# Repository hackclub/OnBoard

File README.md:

# **<h2>Onboard has ended now :/ <br> But much more to come! Stay tuned :). [Sign up here.](https://forms.hackclub.com/t/xtYYcGvNTCus)<h2>**

# OnBoard - Get a $100 grant and make a PCB!

> "I’m so glad that young people can create things like PC boards online. May your creativity have no limits!”
>
> _– [Steve Wozniak](https://en.wikipedia.org/wiki/Steve_Wozniak), Apple co-founder endorsing Hack Club OnBoard_

It's easier than ever for high school students to get involved with programming; all you need is a computing device and internet access. Yet, *it's not the same for hardware*. While PCB fabs have greatly increased the accessibility for professionally done boards, there is still no clear way for high school students to jump in. This is where OnBoard comes in.

---

Every student will receive up to $100 to cover PCB manufacturing costs, and join a community of peers– some more beginner and some more experienced.

## Requirements

Every design/submission needs to meet the following constraints to be approved:

- Unique and open-source design
- Must be orderable on JLCPCB or other [approved vendor](https://github.com/hackclub/OnBoard/blob/main/docs/VENDORS.md)
- Must be in high school or younger[^1][^2][^3] and show proof of school enrollment to submit

[^1]: Home school still counts!
[^2]: If you left high school early you can also submit.
[^3]: If you need help with ideas for proof of age, ask in our Slack and we'll help you out! [here](https://hackclub.com/slack/?event=onboard)

## Getting Started

> You can also go through a video with instructions on how to submit your grant!
>
> 

### Star the repo (Optional)

To follow the repo for updates and show you're participating, click the "star" button on the [`onboard`](https://github.com/hackclub/OnBoard/) repo.

### 1. Join `#electronics` on Slack!

Our [`#electronics`](https://hackclub.slack.com/archives/C0587U78RK4) channel[^4] is where the party is getting started! If you haven't already joined, make sure to add yourself to the channel. And for those who are new to the Hack Club slack, sign up to our community of 13k+ makers through [here](https://hackclub.com/slack/?event=onboard) (don't worry, there isn't an application).

[^4]: This link only works after you've joined the slack. Make sure to get an invite [here](https://hackclub.com/slack/?event=onboard) first.

Perhaps ping a little hello to `@Kevin Yang`?

### 2. Design a Board!

It's design time! If you've done this before, you can skip ahead to step 3. Most people reading this will be new to PCB design, so we've made a simple tutorial on making an example board.

Check out our [PCB tutorials](https://jams.hackclub.com/tag/pcb), where you'll make a design from scratch in a free online editor. This is jumping in the deep end- it won't explain everything, but it will give you a taste of what's possible. By the end you probably won't understand _what_ you did or _why_ you did it, but you will have a working design for a board and you'll know how to **tweak** and **edit** the design to make it your own.

_If you get stuck on these tutorials, or want more example projects to learn from, post in the Slack channel to hear from others going on their journeys._

### 3. Upload to a Vendor and Take a Screenshot

Upload your Gerber files to [JLCPCB.com](https://jlcpcb.com/) and add them to your cart. JLCPCB is the default PCB manufacturer, but you can shop around [^5] if there's a specific one you want to use [^6]. Ensure you complete the checkout process by entering your address and selecting a shipping method. Once completed, take a screenshot with all the final costs and shipping!
> If you're curious what all the settings are about or how to order for assembly, check out our [`ordering_from_JLCPCB.md`](./docs/ordering_from_JLCPCB.md) doc!
> To avoid excess shipping fees or customs, check out [`the Shipping Tips`](./community/shipping.md) doc!

It should look like this:

**Note:** Your screenshot is **VITAL** since your project cannot be approved without it. You'll include the screenshot in your PR later.

[^5]: Don't know which ones you can use? Check out [`VENDORS.md`](./docs/VENDORS.md) for more info!
[^6]: If outside the US you may be charged customs which aren't covered by the grant! Check beforehand.

### 4. Fork!

Fork the [`onboard`](https://github.com/hackclub/OnBoard/) repo! This is the where you'll add your project files and eventually PR from!

### 5. Add Your Design to Your Project Repo

From your fork of `OnBoard`, create a folder with your project name under `OnBoard/projects`. To do this, go to the projects folder and click `Create new file`.

Then in the box labeled `name your file...`, type in `PROJECT_NAME/README.md`. This creates a README file under a folder called named after your project.

After this, copy and paste the contents of [`TEMPLATE.md`](./projects/!Template/TEMPLATE.md?plain=1) into the text editor and fill it out!

Once your done, press the big green `Commit changes` button to save!

With your README filled out, head over to add files to begin uploading your Gerber, design files, and screen shot of vendor approval.

In all, you should have the following files under your project folder:
- [ ] `README.md`: A filled out [`TEMPLATE.md`](./projects/!Template/TEMPLATE.md?plain=1), renamed to `README.md`
- [ ] `cart.png`: A [screenshot](./docs/images/ordering/cart.png) of your order details
- [ ] `gerber.zip`: This should be the file that you send off to the vendor.
- [ ] `schematic.pdf`: Export the schematic from your EDA program as a PDF.
    - Go to "File > Export > PDF" **in EasyEDA's Schematic tab** for this.
- [ ] `src/`: Make a folder called `src` and Whatever format your designer outputs should be included.
    - For **EasyEDA STD**, you need to File > Export > EasyEDA two JSON files - one from the schematic tab and one from the PCB tab.
      - *Optionally*, for EasyEDA STD, export a 3D Model as `.obj` as save it to the `/src` folder 

    - For **KiCad**, read the [Submitting for KiCad](docs/kicad-submission.md), add the `.kicad_pcb`, `.kicad_sch` and `.kicad_pro` files to your `/src` folder.
      - What is **KiCad**? See [KiCad for Beginners](docs/KiCad_Beginner_Guide.md) for a mini tutorial on how to use.
    - Or `design.json`, `design.sch`, `design.brd`, etc for other PCB Editors.

Ensure your file names are exactly the same as above.

Your PR should have a structure like this:

| EasyEDA STD | KiCad |
| ----------- | ----------- |
 | 
----

If you have all the above, you're done with this step!

### 6. Create a PR!

Once you've uploaded your files, you can merge them to the main repo through a pull request! Under the contribute tab of your forked repo, click the big green `Open pull request`.

That will bring you to the main repo, where you'll initiate a pull request. Follow the checklist, we'll then review your PR and you'll be off to the races!

### 7. Get approval and order your board!

Once you submit your PR, it needs two approvals:
- One verifying your high school enrollment documents, from HCB.
- Another one from the engineering team, checking that your design follows the grant requirements.

These reviews typically take 24-48 business hours, and if everything is correct, we'll merge your pull request!

After your pull request gets merged, it can take up to 24 business hours for you to receive an email from HCB with a virtual credit card. Make sure to check your spam folder. Then, you can order your board!

### 8. Ship it!

Post photos of your board in [`#electronics`](https://hackclub.slack.com/archives/C056AMWSFKJ)! We can't wait to see what you make!

## Example Projects

- [PCB Business Card with NFC, "Hackercard"](https://jams.hackclub.com/jam/hacker-card)
- [Build a USB Hub](https://jams.hackclub.com/batch/usb-hub)
- [Make a Digital Level](https://jams.hackclub.com/batch/sparkletilt-pcb)

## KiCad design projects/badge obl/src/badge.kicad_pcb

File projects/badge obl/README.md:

---
name: "Souptik Samanta"
slack_handle: "@Souptik Samanta"
github_handle: "@Souptik-Samanta"
tutorial: # Link to the tutorial if you used one
wokwi: # Link to the Wokwi project if you're submitting for Hacky Holidays
---

# YOUR PROJECT NAME

PCB ADGE

17

hard af took so many revs to finish

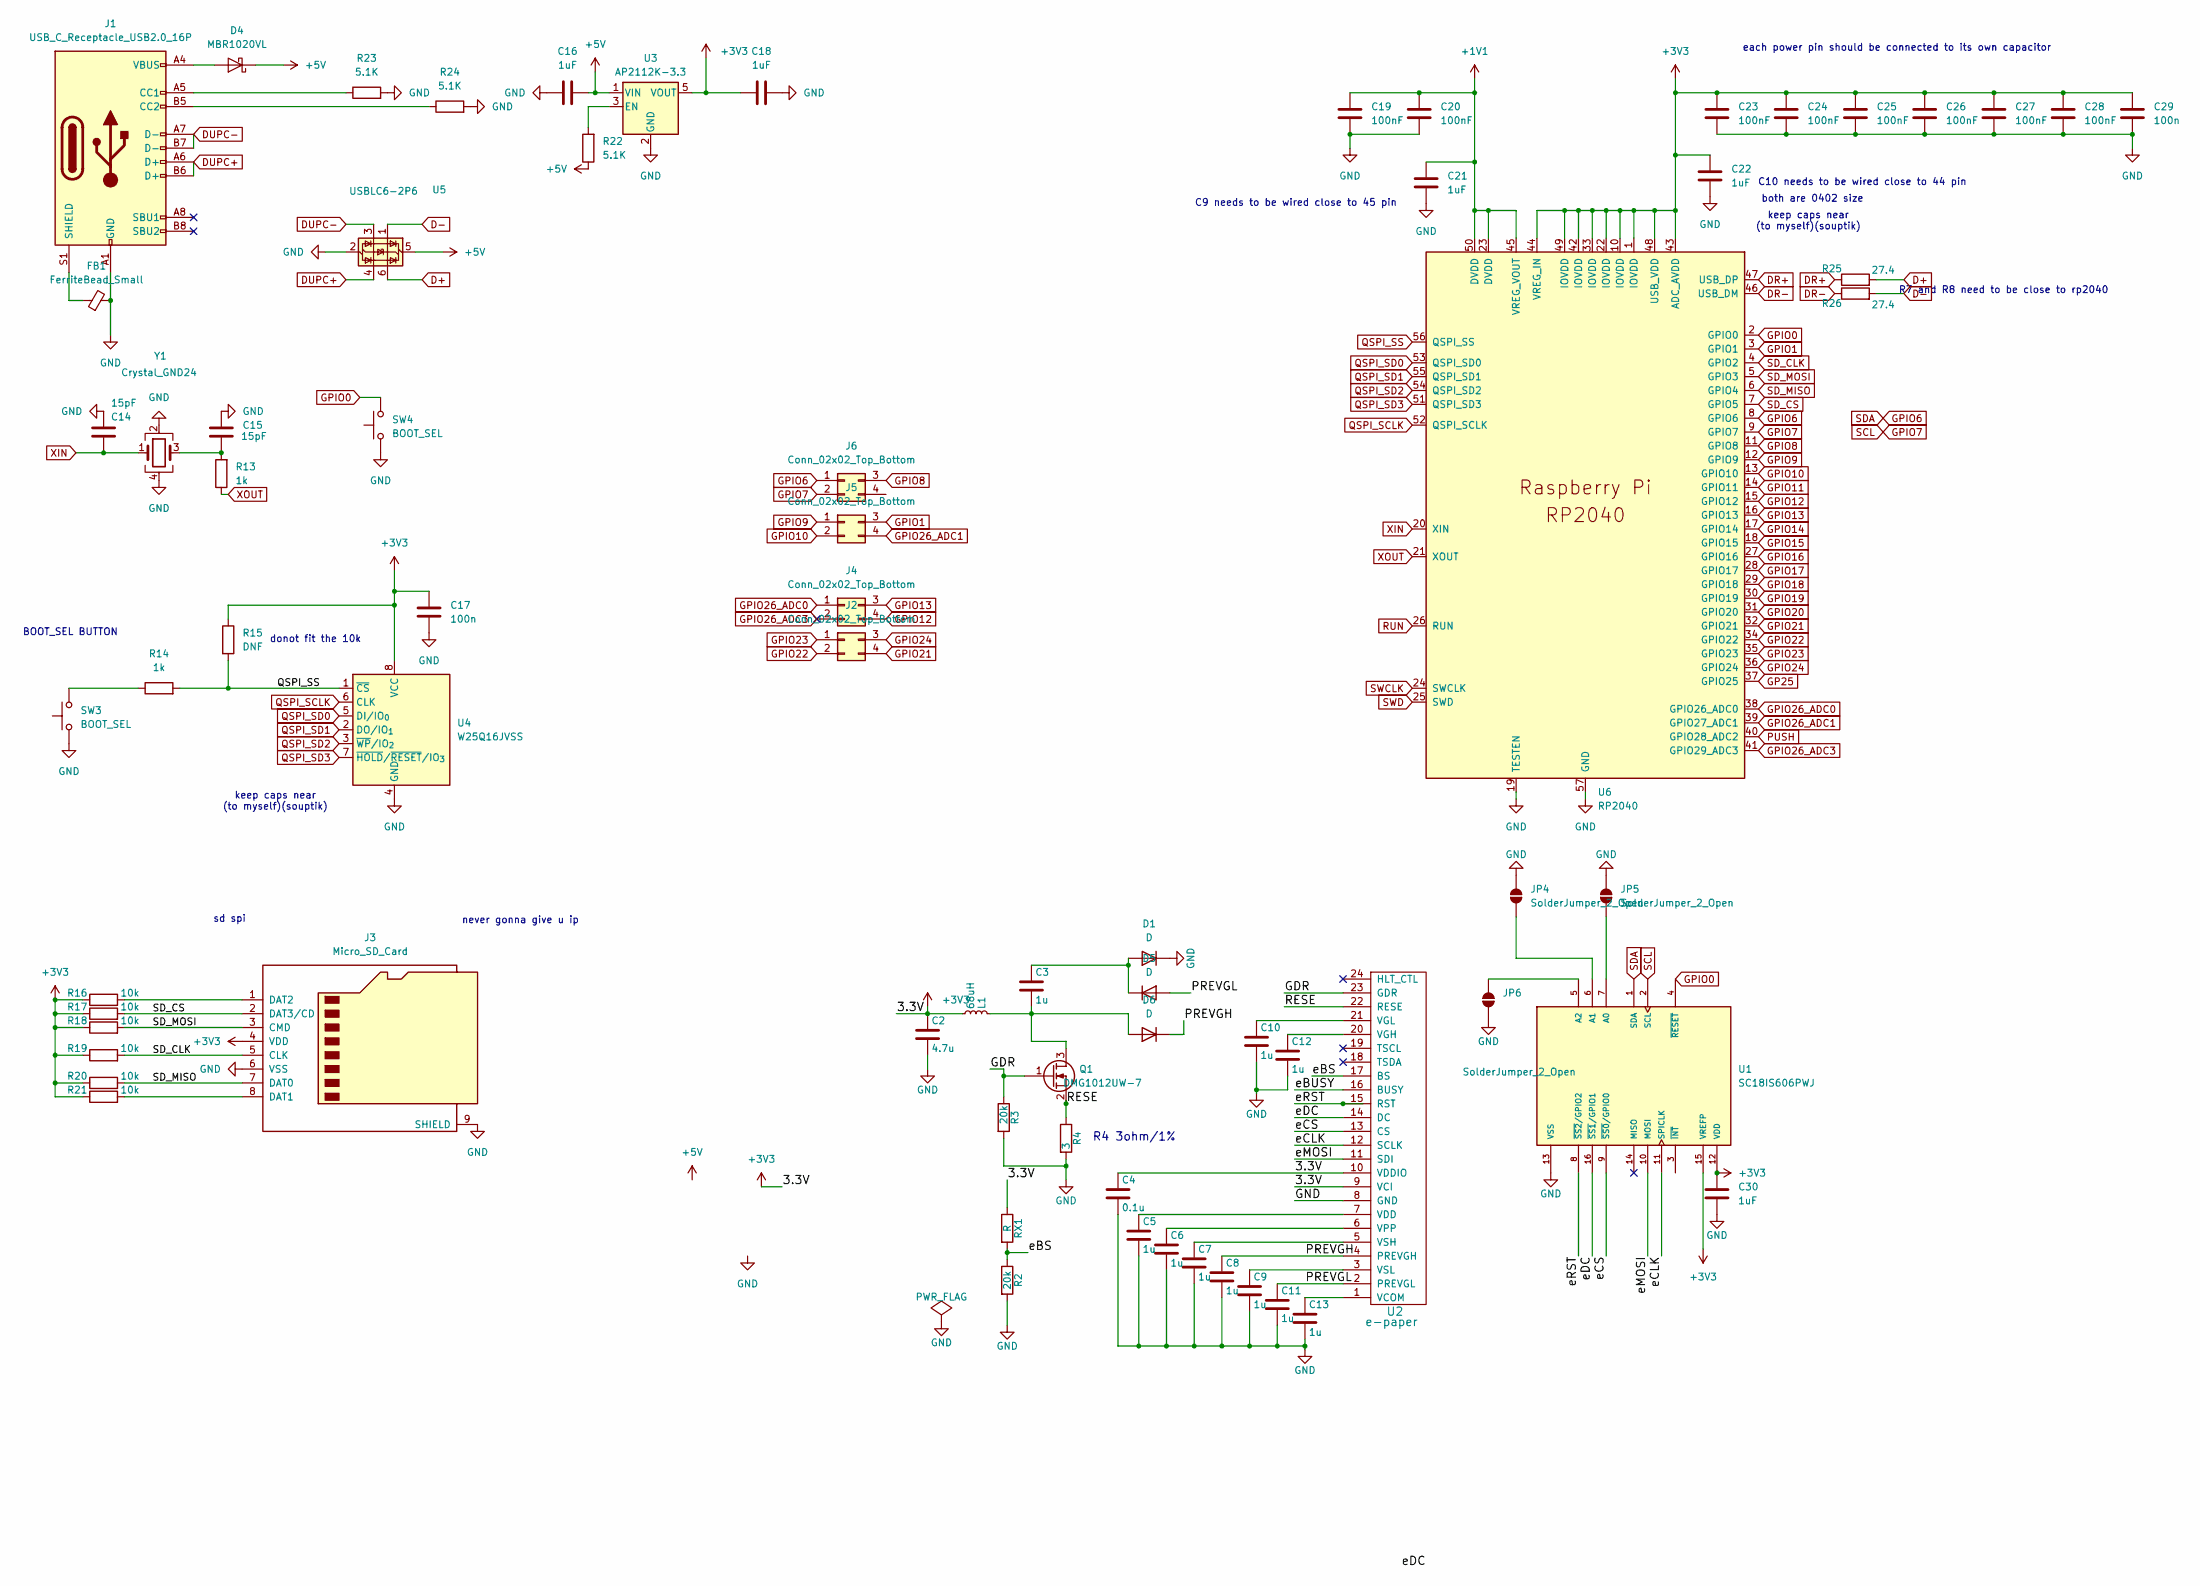
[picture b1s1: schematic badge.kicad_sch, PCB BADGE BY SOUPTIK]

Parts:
C2: 4.7u; C_0201_0603Metric
C3, C5, C6, C7, C8, C9, C10, C11, C12, C13: 1u; C_0201_0603Metric
C4: 0.1u; C_0201_0603Metric
C14, C15: 15pF; C_0402_1005Metric
C16, C18, C21, C22, C30: 1uF; C_0402_1005Metric
C17, C29: 100n; C_0402_1005Metric
C19, C20, C23, C24, C25, C26, C27, C28: 100nF; C_0402_1005Metric
D1, D5, D6: D; Nexperia_CFP3_SOD-123W
D4: MBR1020VL; D_SOD-123F
FB1: FerriteBead_Small; L_0805_2012Metric_Pad1.15x1.40mm_HandSolder
J1: USB_C_Receptacle_USB2.0_16P; USB_C_Receptacle_GCT_USB4105-xx-A_16P_TopMnt_Horizontal
J2, J4, J5, J6: Conn_02x02_Top_Bottom; PinHeader_2x02_P1.00mm_Vertical_SMD
J3: Micro_SD_Card; microSD_HC_Molex_47219-2001
JP4, JP5, JP6: SolderJumper_2_Open; SolderJumper-2_P1.3mm_Open_RoundedPad1.0x1.5mm
L1: 68uH; L_0805_2012Metric_Pad1.05x1.20mm_HandSolder
Q1: DMG1012UW-7; TSOT-23
R2, R3: 20k; R_0805_2012Metric_Pad1.20x1.40mm_HandSolder
R4: 3; R_0805_2012Metric_Pad1.20x1.40mm_HandSolder
R13, R14: 1k; R_0805_2012Metric_Pad1.20x1.40mm_HandSolder
R15: DNF; R_0805_2012Metric_Pad1.20x1.40mm_HandSolder
R16, R17, R18, R19, R20, R21: 10k; R_0805_2012Metric_Pad1.20x1.40mm_HandSolder
R22, R23, R24: 5.1K; R_0805_2012Metric_Pad1.20x1.40mm_HandSolder
R25, R26: 27.4; R_0805_2012Metric_Pad1.20x1.40mm_HandSolder
RX1: R; R_0805_2012Metric_Pad1.20x1.40mm_HandSolder
SW3, SW4: BOOT_SEL; SW_Push_SPST_NO_Alps_SKRK; LCSC C318884
U1: SC18IS606PWJ; SOP65P640X110-16N; PARTREV 1.0
U2: e-paper; 24pin0.5mm
U3: AP2112K-3.3; SOT-23-5
U4: W25Q16JVSS; SOIC-8_5.3x5.3mm_P1.27mm
U5: USBLC6-2P6; SOT-666
U6: RP2040; QFN-56-1EP_7x7mm_P0.4mm_EP3.2x3.2mm
Y1: Crystal_GND24; Crystal_SMD_Abracon_ABM8G-4Pin_3.2x2.5mm

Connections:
+1V1: C19.1, C20.1, C21.1, U6.23 (DVDD), U6.45 (VREG_VOUT), U6.50 (DVDD)
+3V3: C2.1, C4.1, C17.1, C18.2, C22.1, C23.1, C24.1, C25.1, C26.1, C27.1, C28.1, C29.1, C30.1, J3.4 (VDD), L1.2, R15.1, R16.1, R17.1, R18.1, R19.1, R20.1, R21.1, RX1.1, U1.12 (VDD), U1.15 (VREFP), U2.9 (VCI), U2.10 (VDDIO), U3.5 (VOUT), U4.8 (VCC), U6.1 (IOVDD), U6.10 (IOVDD), U6.22 (IOVDD), U6.33 (IOVDD), U6.42 (IOVDD), U6.43 (ADC_AVDD), U6.44 (VREG_IN), U6.48 (USB_VDD), U6.49 (IOVDD)
+5V: C16.1, D4.1 (K), R22.1, U3.1 (VIN), U5.5 (VBUS)
/GDR: Q1.1 (G), R3.1, U2.23 (GDR)
/PREVGH: C8.1, D6.1 (K), U2.4 (PREVGH)
/PREVGL: C11.1, D5.2 (A), U2.2 (PREVGL)
/RESE: Q1.2 (S), R4.1, U2.22 (RESE)
/eBS: R2.1, RX1.2, U2.17 (BS)
/eBUSY: U2.16 (BUSY)
/eCLK: U1.11 (SPICLK), U2.12 (SCLK)
/eCS: U1.9 (~SS0/GPIO0), U2.13 (CS)
/eDC: U1.16 (~SS1/GPIO1), U2.14 (DC)
/eMOSI: U1.10 (MOSI), U2.11 (SDI)
/eRST: U1.8 (~SS2/GPIO2), U2.15 (RST)
D+: R25.2, U5.6 (I/O1)
D-: R26.2, U5.1 (I/O1)
DR+: R25.1, U6.47 (USB_DP)
DR-: R26.1, U6.46 (USB_DM)
DUPC+: J1.A6 (D+), J1.B6 (D+), U5.4 (I/O2)
DUPC-: J1.A7 (D-), J1.B7 (D-), U5.3 (I/O2)
GND: C2.2, C4.2, C5.2, C6.2, C7.2, C8.2, C9.2, C10.2, C11.2, C12.2, C13.2, C14.2, C15.2, C16.2, C17.2, C18.1, C19.2, C20.2, C21.2, C22.2, C23.2, C24.2, C25.2, C26.2, C27.2, C28.2, C29.2, C30.2, D1.1 (K), FB1.2, J1.A1 (GND), J1.A12 (GND), J1.B1 (GND), J1.B12 (GND), J3.6 (VSS), J3.9 (SHIELD), JP4.2 (B), JP5.2 (B), JP6.1 (A), R2.2, R3.2, R4.2, R23.2, R24.2, SW3.1, SW4.1, U1.13 (VSS), U2.8 (GND), U3.2 (GND), U4.4 (GND), U5.2 (GND), U6.19 (TESTEN), U6.57 (GND), Y1.2, Y1.4
GP25: U6.37 (GPIO25)
GPIO0: SW4.2, U1.4 (~RESET), U6.2 (GPIO0)
GPIO1: J5.3, U6.3 (GPIO1)
GPIO6: J6.1, U1.1 (SDA), U6.8 (GPIO6)
GPIO7: J6.2, U1.2 (SCL), U6.9 (GPIO7)
GPIO8: J6.3, U6.11 (GPIO8)
GPIO9: J5.1, U6.12 (GPIO9)
GPIO10: J5.2, U6.13 (GPIO10)
GPIO11: U6.14 (GPIO11)
GPIO12: J4.4, U6.15 (GPIO12)
GPIO13: J4.3, U6.16 (GPIO13)
GPIO14: U6.17 (GPIO14)
GPIO15: U6.18 (GPIO15)
GPIO16: U6.27 (GPIO16)
GPIO17: U6.28 (GPIO17)
GPIO18: U6.29 (GPIO18)
GPIO19: U6.30 (GPIO19)
GPIO20: U6.31 (GPIO20)
GPIO21: J2.4, U6.32 (GPIO21)
GPIO22: J2.2, U6.34 (GPIO22)
GPIO23: J2.1, U6.35 (GPIO23)
GPIO24: J2.3, U6.36 (GPIO24)
GPIO26_ADC0: J4.1, U6.38 (GPIO26_ADC0)
GPIO26_ADC1: J5.4, U6.39 (GPIO27_ADC1)
GPIO26_ADC3: J4.2, U6.41 (GPIO29_ADC3)
unnamed: C15.1, R13.2, Y1.3
unnamed: C3.1, D1.2 (A), D5.1 (K)
unnamed: D4.2 (A), J1.A4 (VBUS), J1.A9 (VBUS), J1.B4 (VBUS), J1.B9 (VBUS)
unnamed: C3.2, D6.2 (A), L1.1, Q1.3 (D)
unnamed: J1.A5 (CC1), R23.1
unnamed: J1.B5 (CC2), R24.1
unnamed: FB1.1, J1.S1 (SHIELD)
unnamed: J3.8 (DAT1), R21.2
unnamed: J3.1 (DAT2), R16.2
unnamed: JP4.1 (A), U1.6 (A1)
unnamed: JP5.1 (A), U1.7 (A0)
unnamed: JP6.2 (B), U1.5 (A2)
unnamed: R14.1, SW3.2
unnamed: C13.1, U2.1 (VCOM)
unnamed: C5.1, U2.7 (VDD)
unnamed: C12.1, U2.20 (VGH)
unnamed: C10.1, U2.21 (VGL)
unnamed: C6.1, U2.6 (VPP)
unnamed: C7.1, U2.5 (VSH)
unnamed: C9.1, U2.3 (VSL)
unnamed: R22.2, U3.3 (EN)
PUSH: U6.40 (GPIO28_ADC2)
QSPI_SCLK: U4.6 (CLK), U6.52 (QSPI_SCLK)
QSPI_SD0: U4.5 (DI/IO_{0}), U6.53 (QSPI_SD0)
QSPI_SD1: U4.2 (DO/IO_{1}), U6.55 (QSPI_SD1)
QSPI_SD2: U4.3 (~WP/IO_{2}), U6.54 (QSPI_SD2)
QSPI_SD3: U4.7 (~HOLD/~RESET/IO_{3}), U6.51 (QSPI_SD3)
QSPI_SS: R14.2, R15.2, U4.1 (~CS), U6.56 (QSPI_SS)
RUN: U6.26 (RUN)
SD_CLK: J3.5 (CLK), R19.2, U6.4 (GPIO2)
SD_CS: J3.2 (DAT3/CD), R17.2, U6.7 (GPIO5)
SD_MISO: J3.7 (DAT0), R20.2, U6.6 (GPIO4)
SD_MOSI: J3.3 (CMD), R18.2, U6.5 (GPIO3)
SWCLK: U6.24 (SWCLK)
SWD: U6.25 (SWD)
XIN: C14.1, U6.20 (XIN), Y1.1
XOUT: R13.1, U6.21 (XOUT)

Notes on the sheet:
sd spi
never gonna give u ip
donot fit the 10k
BOOT_SEL BUTTON
C9 needs to be wired close to 45 pin
each power pin should be connected to its own capacitor
keep caps near (to myself)(souptik)
C10 needs to be wired close to 44 pin
R4 3ohm/1%
both are 0402 size
R7 and R8 need to be close to rp2040

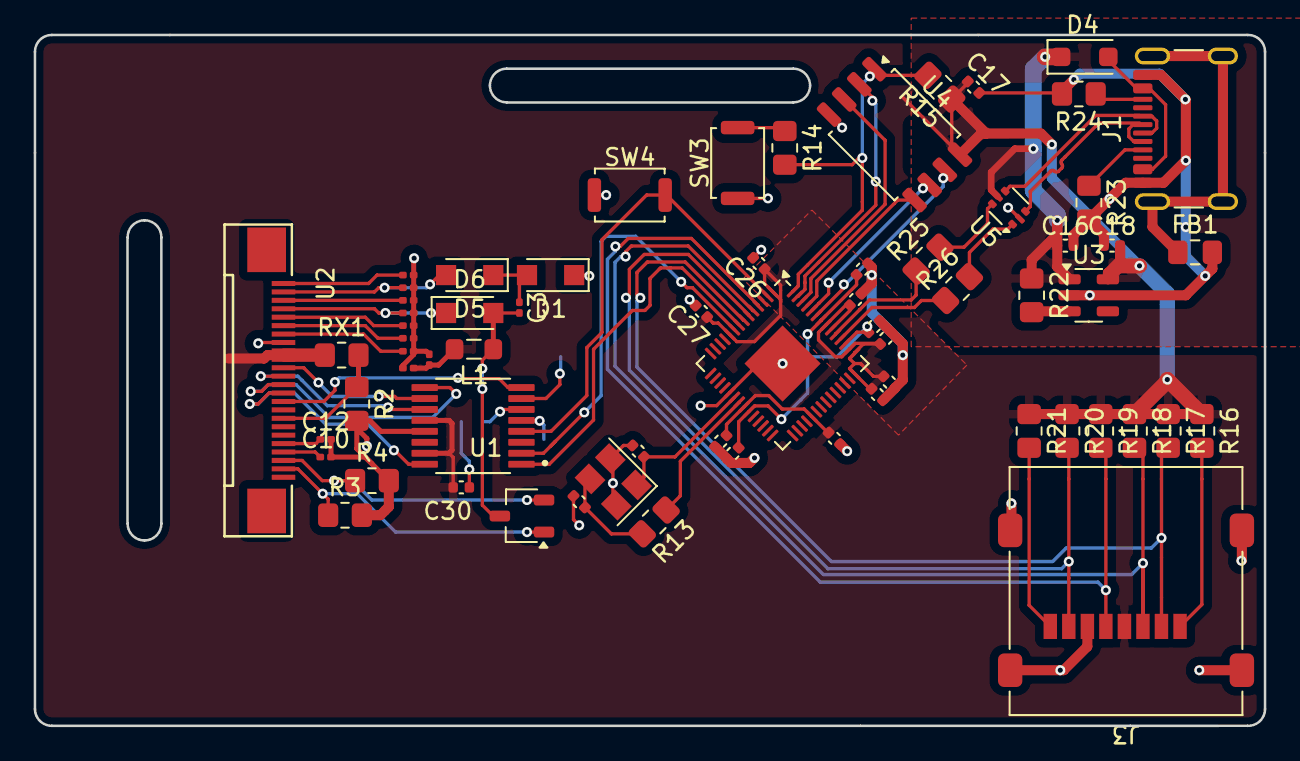
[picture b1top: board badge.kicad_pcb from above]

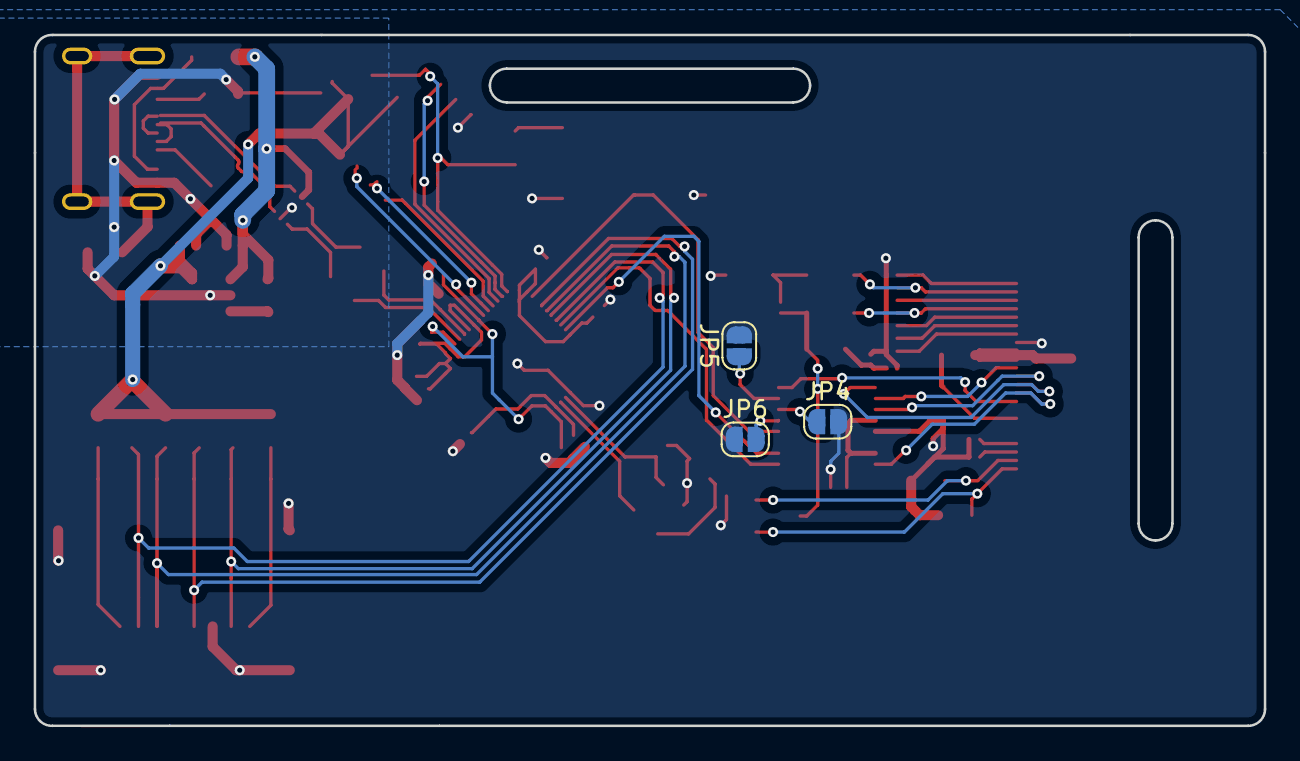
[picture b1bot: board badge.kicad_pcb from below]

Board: 2 copper layers, 73.0 x 41.0 mm, 68 parts (3 on the bottom side), 56 nets.

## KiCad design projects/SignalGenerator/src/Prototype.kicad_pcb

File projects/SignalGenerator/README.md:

---
name: "FIRST LAST"
slack_handle: "@bhallachirag044"
github_handle: "@Chiragb16"
tutorial: # Link to the tutorial if you used one
wokwi: # Link to the Wokwi project if you're submitting for Hacky Holidays
---

# SIGNAL GENEARTOR

<!-- Describe your board in 2-3 sentences. What are you making? What will it do? -->
I am making a signal generator that uses NRF and ESP to generate a signal frequency for 2.4GHz.

<!-- How much is it going to cost? -->

$98(with assembly from JLCPCB)
$33(without assembly)
<!-- Tell us a little bit about your design process. What were some challenges? What helped? ***Totally optional*** -->

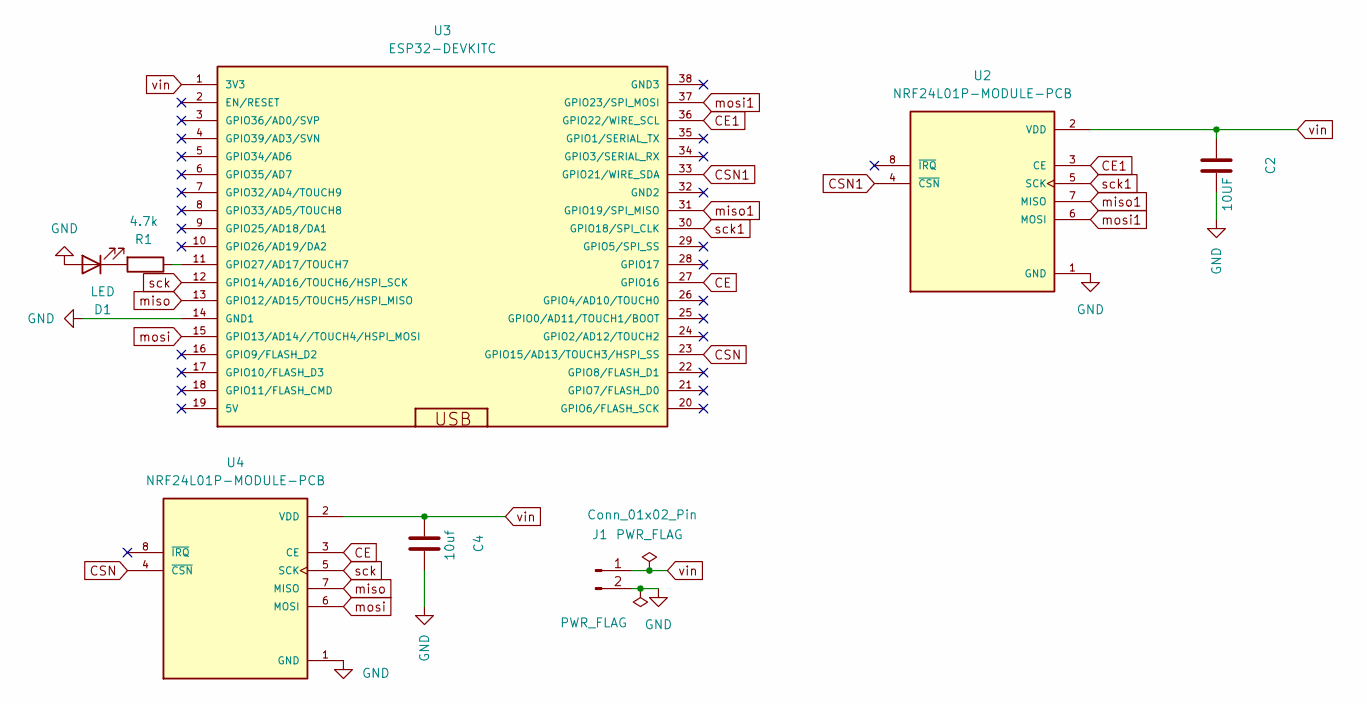
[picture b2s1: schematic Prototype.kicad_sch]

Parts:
C2: 10UF; C_Radial_D5.0mm_H11.0mm_P2.00mm
C4: 10uf; C_Radial_D5.0mm_H11.0mm_P2.00mm
D1: LED; LED_D5.0mm
J1: Conn_01x02_Pin; PinHeader_1x02_P2.54mm_Vertical
R1: 4.7k; R_Axial_DIN0207_L6.3mm_D2.5mm_P7.62mm_Horizontal
U2, U4: NRF24L01P-MODULE-PCB; XCVR_NRF24L01P-MODULE-PCB; PARTREV 1.0
U3: ESP32-DEVKITC

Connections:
CE: U3.27 (GPIO16), U4.3 (CE)
CE1: U2.3 (CE), U3.36 (GPIO22/WIRE_SCL)
CSN: U3.23 (GPIO15/AD13/TOUCH3/HSPI_SS), U4.4 (~CSN)
CSN1: U2.4 (~CSN), U3.33 (GPIO21/WIRE_SDA)
GND: C2.2, C4.2, D1.2 (A), J1.2, U2.1 (GND), U3.14 (GND1), U4.1 (GND)
unnamed: D1.1 (K), R1.2
unnamed: R1.1, U3.11 (GPIO27/AD17/TOUCH7)
miso: U3.13 (GPIO12/AD15/TOUCH5/HSPI_MISO), U4.7 (MISO)
miso1: U2.7 (MISO), U3.31 (GPIO19/SPI_MISO)
mosi: U3.15 (GPIO13/AD14//TOUCH4/HSPI_MOSI), U4.6 (MOSI)
mosi1: U2.6 (MOSI), U3.37 (GPIO23/SPI_MOSI)
sck: U3.12 (GPIO14/AD16/TOUCH6/HSPI_SCK), U4.5 (SCK)
sck1: U2.5 (SCK), U3.30 (GPIO18/SPI_CLK)
vin: C2.1, C4.1, J1.1, U2.2 (VDD), U3.1 (3V3), U4.2 (VDD)

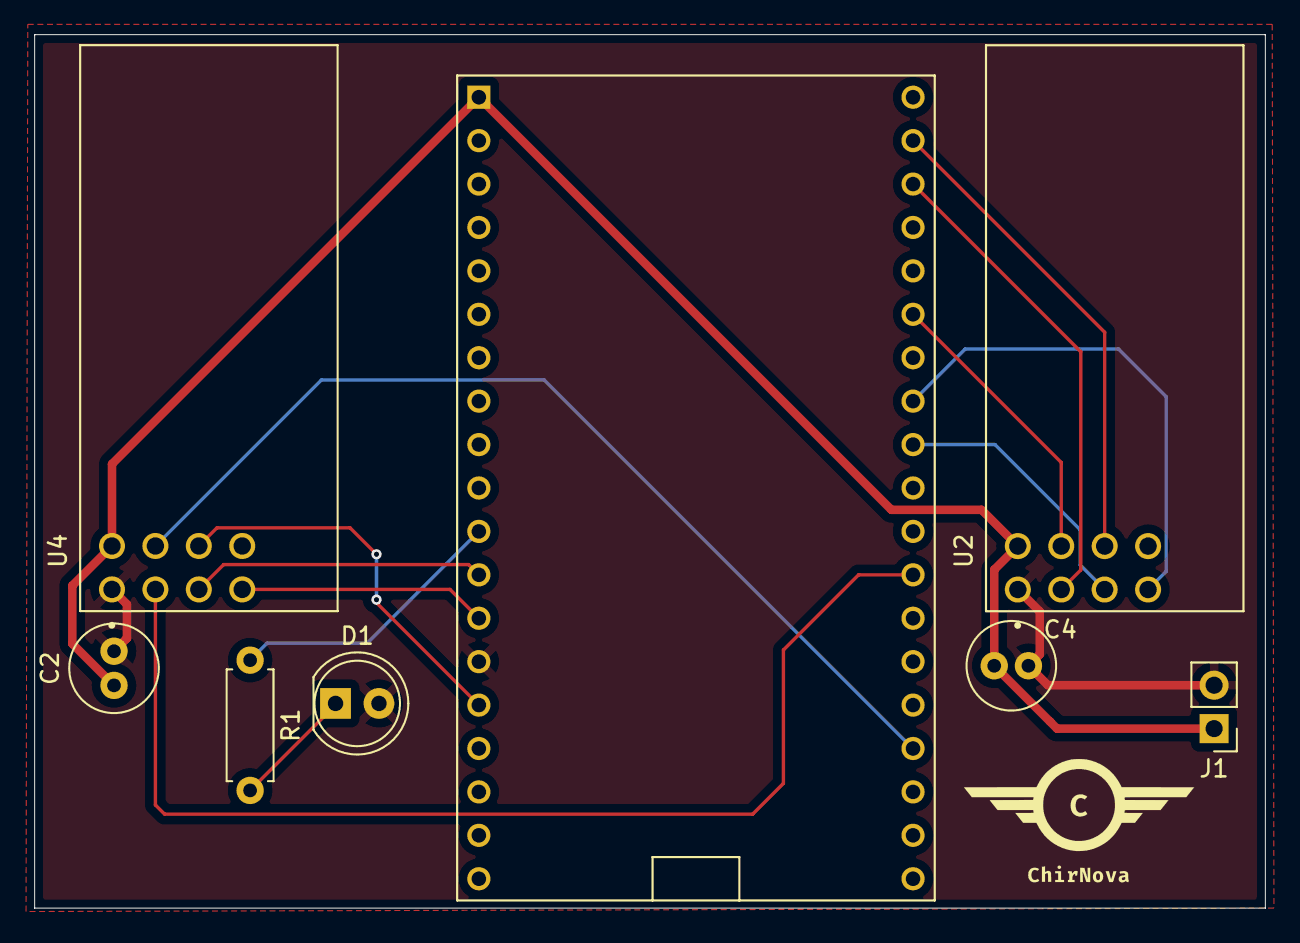
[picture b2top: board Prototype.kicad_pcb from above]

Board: 2 copper layers, 72.0 x 51.1 mm, 8 parts (0 on the bottom side), 14 nets.

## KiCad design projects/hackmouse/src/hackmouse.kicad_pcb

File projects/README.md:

---
name: "Daniel Pilkington"
slack_handle: "@Daniel Pilkington"
github_handle: "@danjpilkE"
tutorial: # https://jams.hackclub.com/jam/hacker-card
wokwi: # Link to the Wokwi project if you're submitting for Hacky Holidays
---

# Card

<!-- Describe your board in 2-3 sentences. What are you making? What will it do? -->
A black PCB board with name, github and email
<!-- How much is it going to cost? -->
$21.68
<!-- Tell us a little bit about your design process. What were some challenges? What helped? ***Totally optional*** -->

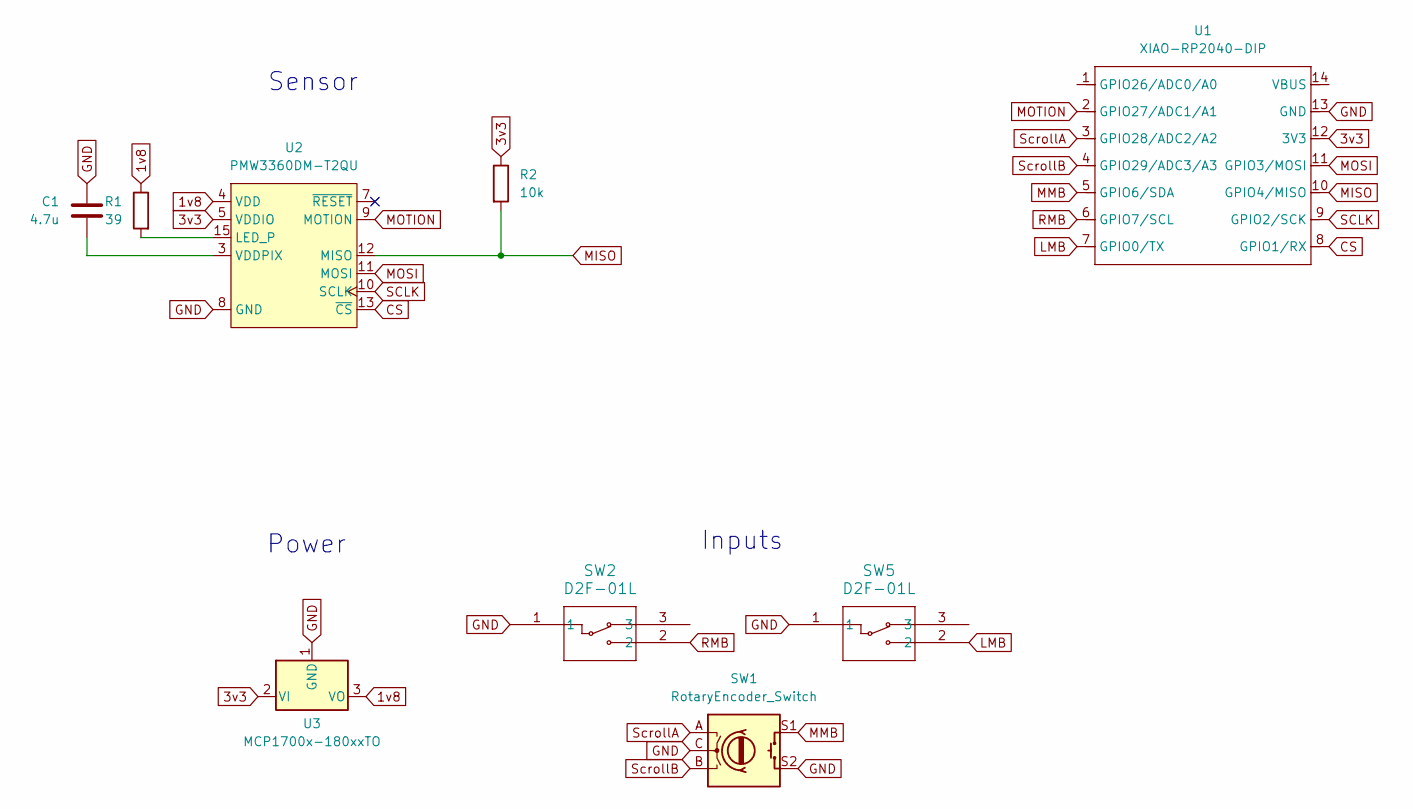
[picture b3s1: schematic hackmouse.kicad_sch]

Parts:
C1: 4.7u; CP_Radial_D6.3mm_P2.50mm
R1: 39; R_Axial_DIN0204_L3.6mm_D1.6mm_P7.62mm_Horizontal
R2: 10k; R_Axial_DIN0204_L3.6mm_D1.6mm_P7.62mm_Horizontal
SW1: RotaryEncoder_Switch; RotaryEncoder_EC11B-Horizontal-Dual
SW2, SW5: D2F-01L; D2F-01L_OMR
U1: XIAO-RP2040-DIP
U2: PMW3360DM-T2QU; PMW3360DM-T2QU 16Pin
U3: MCP1700x-180xxTO; TO-92_Inline

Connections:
1v8: R1.1, U2.4 (VDD), U3.3 (VO)
3v3: R2.1, U1.12 (3V3), U2.5 (VDDIO), U3.2 (VI)
CS: U1.8 (GPIO1/RX), U2.13 (~CS)
GND: C1.1, SW1.C, SW1.S2, SW2.1, SW5.1, U1.13 (GND), U2.8 (GND), U3.1 (GND)
LMB: SW5.2, U1.7 (GPIO0/TX)
MISO: R2.2, U1.10 (GPIO4/MISO), U2.12 (MISO)
MMB: SW1.S1, U1.5 (GPIO6/SDA)
MOSI: U1.11 (GPIO3/MOSI), U2.11 (MOSI)
MOTION: U1.2 (GPIO27/ADC1/A1), U2.9 (MOTION)
unnamed: R1.2, U2.15 (LED_P)
unnamed: C1.2, U2.3 (VDDPIX)
RMB: SW2.2, U1.6 (GPIO7/SCL)
SCLK: U1.9 (GPIO2/SCK), U2.10 (SCLK)
ScrollA: SW1.A, U1.3 (GPIO28/ADC2/A2)
ScrollB: SW1.B, U1.4 (GPIO29/ADC3/A3)

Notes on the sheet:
Inputs
Sensor
Power

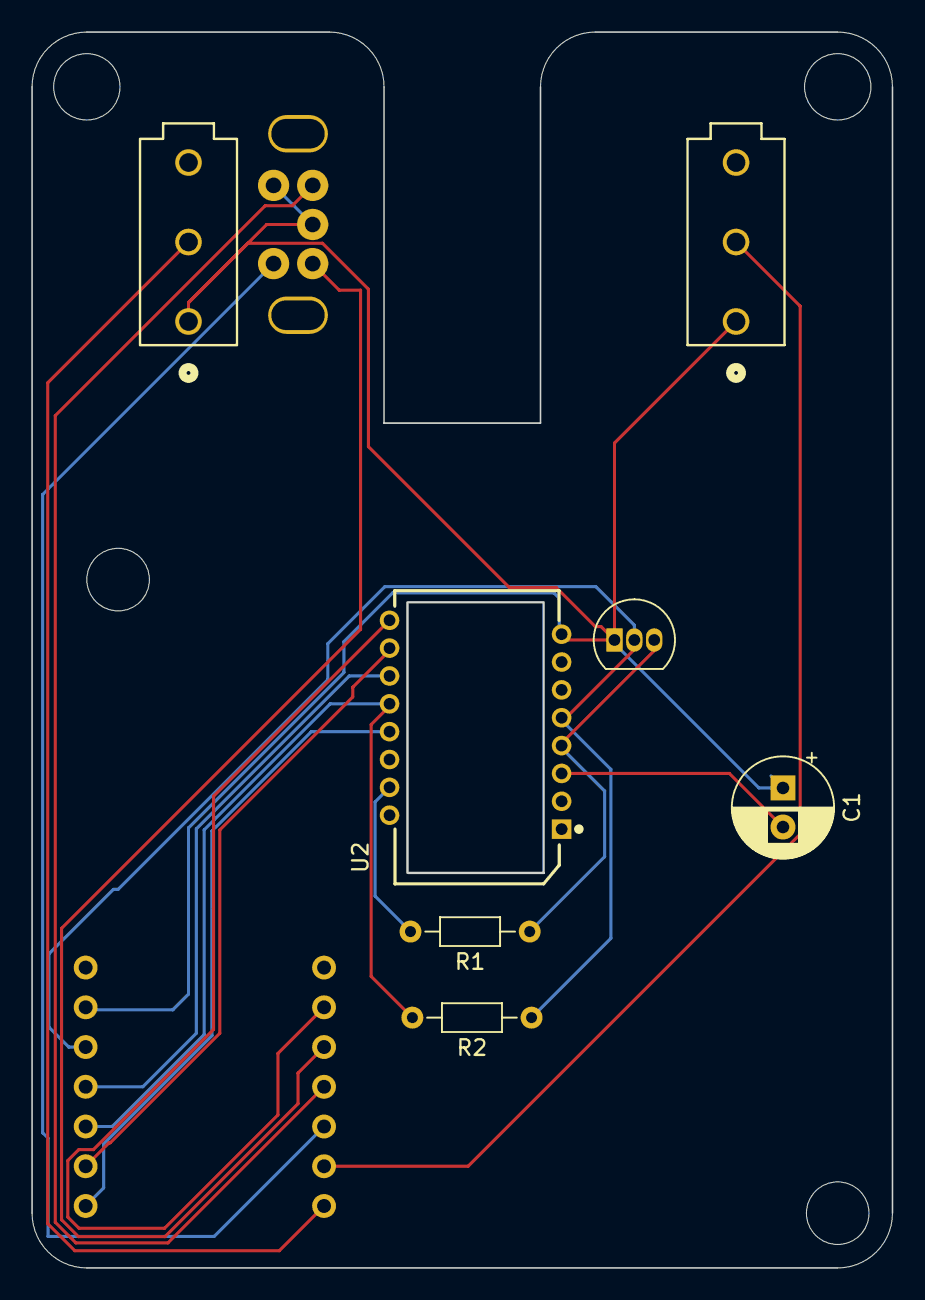
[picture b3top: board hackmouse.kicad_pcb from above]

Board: 2 copper layers, 55.0 x 79.0 mm, 9 parts (1 on the bottom side), 15 nets.
